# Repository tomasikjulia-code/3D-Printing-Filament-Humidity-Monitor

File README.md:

# 3D Printing Filament Humidity Monitor

Board designed to monitor storage conditions for 3D printing filaments. Using the **DHT22** sensor, this board ensures your hygroscopic materials stay within the optimal humidity range to prevent printing defects.

---

## Why It Matters
Moisture is the enemy of high-quality 3D prints. This project helps you:
* **Prevent Stringing & Bubbles:** Identify when filament needs drying.
* **Monitor Dryboxes:** Real-time tracking of internal humidity in sealed containers.
* **Optimize Print Quality:** Ensure consistent extrusion by maintaining dry material.

---

## Features
* **Sensor:** DHT22 High-accuracy capacitive humidity and temperature sensor.
* **Microcontroller:** STM32F103C8Tx.
* **Local Display:** Support for I2C OLED (SH1106) to check status at a glance.
* **Power:** Powered by Li-Po accumulator with charger TP4056 USB-C

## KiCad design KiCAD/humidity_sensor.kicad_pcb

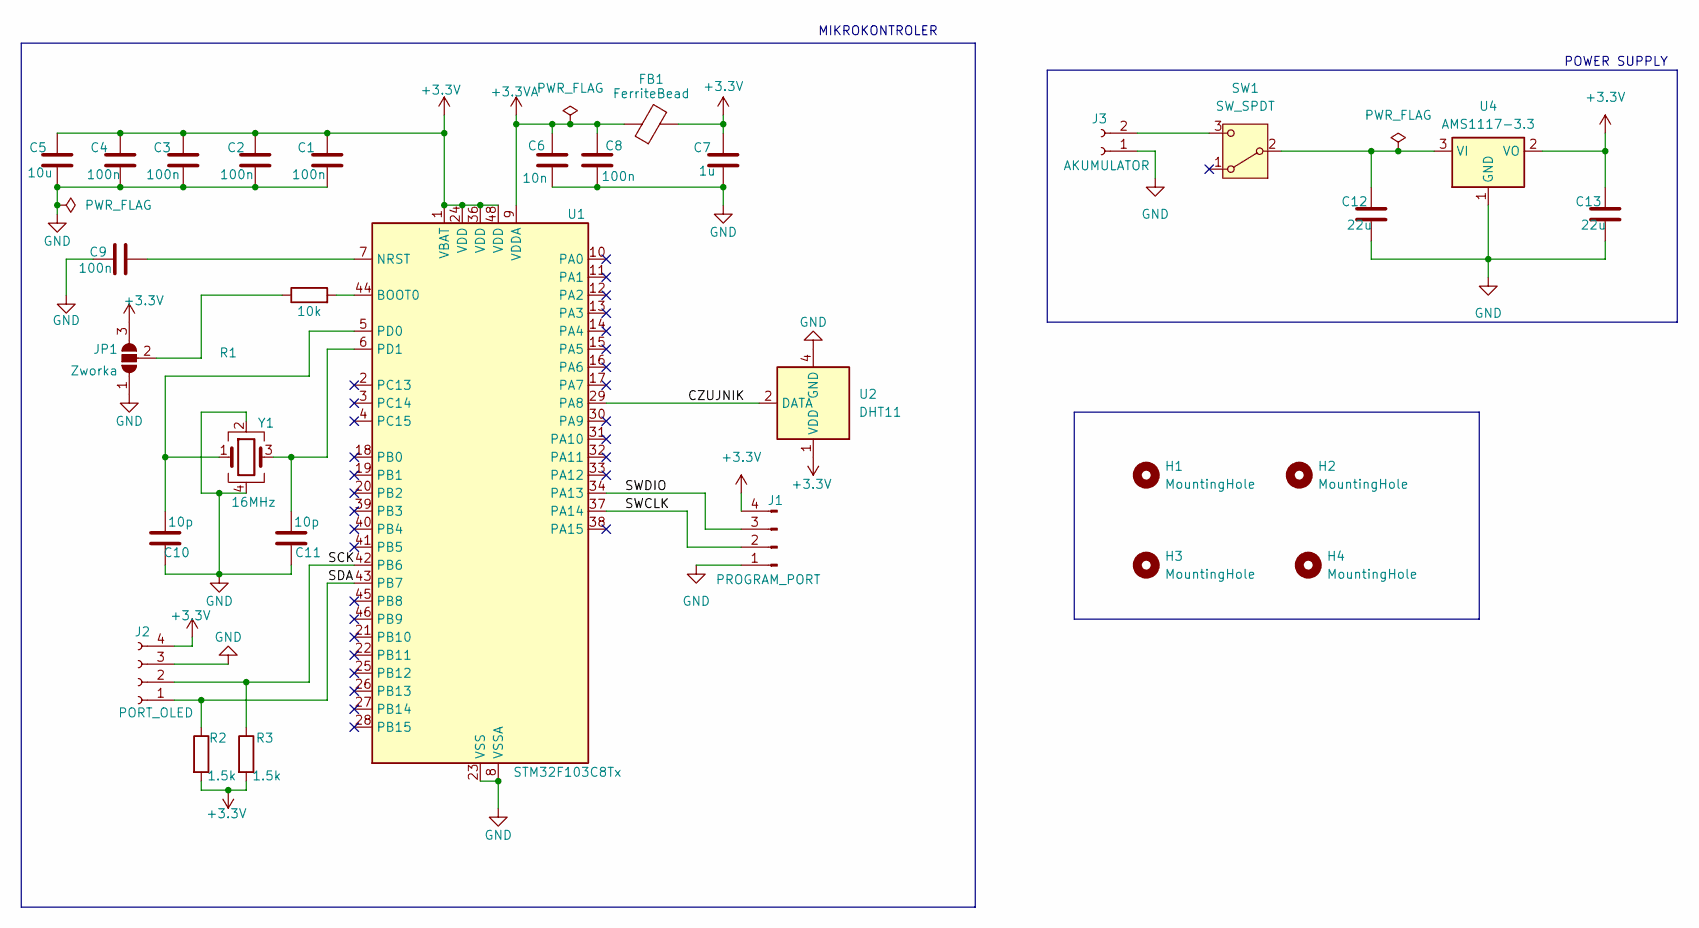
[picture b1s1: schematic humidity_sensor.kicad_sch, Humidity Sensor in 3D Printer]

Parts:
C1, C2, C3, C4, C8, C9: 100n; C_0402_1005Metric
C5: 10u; C_0402_1005Metric
C6: 10n; C_0402_1005Metric
C7: 1u; C_0402_1005Metric
C10, C11: 10p; C_0402_1005Metric
C12, C13: 22u; C_0805_2012Metric
FB1: FerriteBead; L_0603_1608Metric
H1, H2, H3, H4: MountingHole; MountingHole_3.2mm_M3
J1: PROGRAM_PORT; JST_PH_S4B-PH-K_1x04_P2.00mm_Horizontal
J2: PORT_OLED; PinSocket_1x04_P2.54mm_Vertical
J3: AKUMULATOR; PinSocket_1x02_P2.54mm_Vertical
JP1: Zworka; SolderJumper-3_P1.3mm_Open_RoundedPad1.0x1.5mm
R1: 10k; R_0402_1005Metric
R2, R3: 1.5k; R_0402_1005Metric
SW1: SW_SPDT; SW_E-Switch_EG1224_SPDT_Angled
U1: STM32F103C8Tx; LQFP-48_7x7mm_P0.5mm
U2: DHT11; Aosong_DHT11_5.5x12.0_P2.54mm
U4: AMS1117-3.3; SOT-223-3_TabPin2
Y1: 16MHz; Crystal_SMD_3225-4Pin_3.2x2.5mm

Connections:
+3.3V: C1.1, C2.1, C3.1, C4.1, C5.1, C7.1, C13.1, FB1.2, J1.4, J2.4, JP1.3 (B), R2.2, R3.2, U1.1 (VBAT), U1.24 (VDD), U1.36 (VDD), U1.48 (VDD), U2.1 (VDD), U4.2 (VO)
+3.3VA: C6.1, C8.1, FB1.1, U1.9 (VDDA)
/CZUJNIK: U1.29 (PA8), U2.2 (DATA)
/SCK: J2.2, R3.1, U1.42 (PB6)
/SDA: J2.1, R2.1, U1.43 (PB7)
/SWCLK: J1.2, U1.37 (PA14)
/SWDIO: J1.3, U1.34 (PA13)
GND: C1.2, C2.2, C3.2, C4.2, C5.2, C6.2, C7.2, C8.2, C9.1, C10.1, C11.1, C12.2, C13.2, J1.1, J2.3, J3.1, JP1.1 (A), U1.8 (VSSA), U1.23 (VSS), U1.35 (VSS), U1.47 (VSS), U2.4 (GND), U4.1 (GND), Y1.2, Y1.4
unnamed: J3.2, SW1.3 (C)
unnamed: JP1.2 (C), R1.1
unnamed: C12.1, SW1.2 (B), U4.3 (VI)
unnamed: R1.2, U1.44 (BOOT0)
unnamed: C9.2, U1.7 (NRST)
unnamed: C10.2, U1.5 (PD0), Y1.1
unnamed: C11.2, U1.6 (PD1), Y1.3

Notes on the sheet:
POWER SUPPLY
MIKROKONTROLER

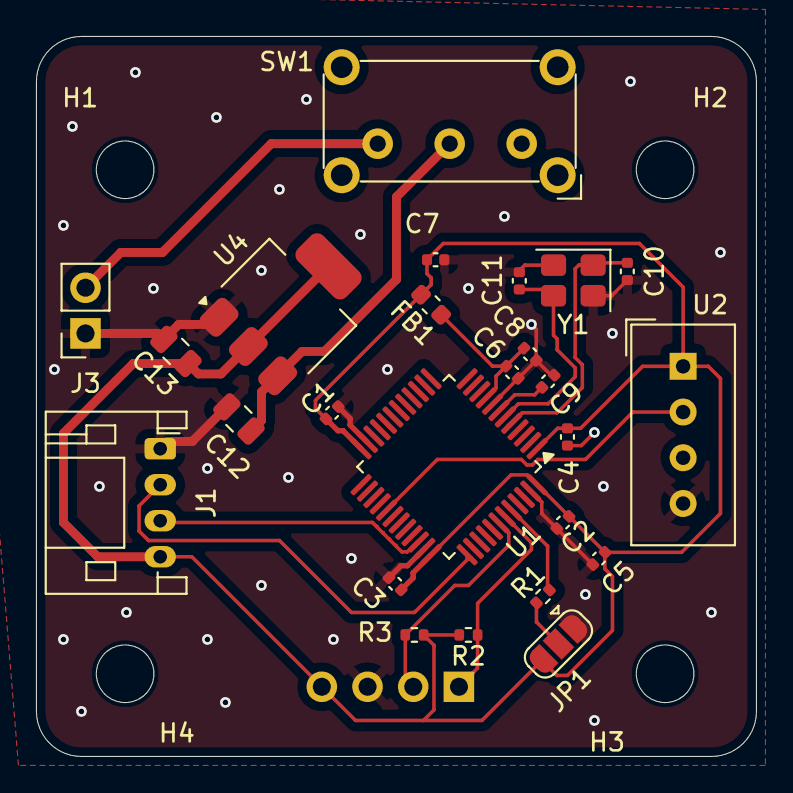
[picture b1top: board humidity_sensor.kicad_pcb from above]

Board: 2 copper layers, 40.0 x 40.0 mm, 30 parts (1 on the bottom side), 15 nets.

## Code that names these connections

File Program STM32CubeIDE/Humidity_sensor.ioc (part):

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Mcu.Name=STM32F103C(8-B)Tx
Mcu.Package=LQFP48
Mcu.UserName=STM32F103C8Tx
PA13.Mode=Serial_Wire
PA13.Signal=SYS_JTMS-SWDIO
PA14.Mode=Serial_Wire
PA14.Signal=SYS_JTCK-SWCLK
PA8.GPIOParameters=PinState,GPIO_PuPd,GPIO_Label
PA8.GPIO_Label=SENSOR
PA8.GPIO_PuPd=GPIO_PULLUP
PA8.PinState=GPIO_PIN_SET
PA8.Signal=GPIO_Output
PB6.Mode=I2C
PB6.Signal=I2C1_SCL
PB7.Mode=I2C
PB7.Signal=I2C1_SDA
PD0-OSC_IN.Mode=HSE-External-Oscillator
PD0-OSC_IN.Signal=RCC_OSC_IN
PD1-OSC_OUT.Mode=HSE-External-Oscillator
PD1-OSC_OUT.Signal=RCC_OSC_OUT
RCC.HSE_VALUE=16000000
RCC.SYSCLKFreq_VALUE=64000000
RCC.SYSCLKSource=RCC_SYSCLKSOURCE_PLLCLK
board=custom

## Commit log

2026-01-25 DHT22
